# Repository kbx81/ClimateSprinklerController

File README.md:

# kbx's Climate and Sprinkler Controller

## A DIY Thermostat and/or Sprinkler (Valve) Controller

Here you'll find plans for an ESP32-based controller designed with [ESPHome](https://esphome.io) in mind. It is primarily designed for switching 24-volt AC circuits but it is flexible by design and should be adaptable to other types of electrical workloads.

In the [Preface](PREFACE.md) you will find background information about this project such as how it came to be and some personal thoughts and experiences I've had with home automation through the years.

In the [Hardware](HARDWARE.md) document you will find a general explanation of the theory of operation of a thermostat as well as a design overview of this device, some handy tips (should you choose to build one), construction, usage, and installation detail.

Finally, the [Hardware Detail](HARDWARE_DETAIL.md) document aims to explain why I did what I did -- design decisions, etc.

## Design Versions

At present there are two major "versions" of (iterations on?) the device -- a version that supports an OLED display such as the [SSD1325](https://www.adafruit.com/product/2674) and a version (well, actually three versions) that supports a Nextion touchscreen display. The project files for each can be found in its respective directory:
 - OLED versions:
   - [Version 2 (WROOM)](WROOM/)
   - [Version 3 (WROVER)](WROVER/)
 - Nextion versions:
   - [Nextion 3.5"](WROVER-Nextion3.5/) (contains no switching hardware!)
   - [Nextion 5"](WROVER-Nextion5/)
   - [Nextion 7"](WROVER-Nextion7/)

## PCB and BoMs

The schematic and PCB were drawn in [KiCAD](https://www.kicad.org). I had PCBs fabricated by [Elecrow](https://www.elecrow.com) but nearly any PCB fabricator should be able to manufacture these without any issues.

On [Octopart](https://octopart.com) I have posted a bill of materials (BoM) for each design version:
 - OLED versions:
   - [Version 2 (WROOM)](https://octopart.com/bom-tool/XvGbAePy)
   - [Version 3 (WROVER)](https://octopart.com/bom-tool/vZKpLnMD)
 - Nextion versions:
   - [Nextion 3.5"](https://octopart.com/bom-tool/dj6BW0gV) (contains no switching hardware!)
   - [Nextion 5"](https://octopart.com/bom-tool/kHZhyfjO)
   - [Nextion 7"](https://octopart.com/bom-tool/b5Lb00Zs)

### Important!

**Save money** by reading through the [build guide](HARDWARE.md) **before** you order any parts, as you likely _do not need **every** part in the linked BoMs!_ (For example, there are footprints multiple sensors on each PCB. You do not need all of the sensors!)

## ESPHome Configuration & Code

I've created a separate repository for my [ESPHome](https://esphome.io) [configurations](https://github.com/kbx81/esphome-configs); if you're looking for a starting point/example configuration, please have a look there.

## Legal stuff and License

Everything you see here is provided to you free of charge. You are free to use it however you please within the constraints of the license -- but you do so at your own risk. I accept absolutely no liability if you cause damage to your property, HVAC system, or any other hardware you choose to connect to this device.

The circuit schematics, PCBs and enclosures found here are licensed under the [Creative Commons Attribution-ShareAlike 4.0 International License](http://creativecommons.org/licenses/by-sa/4.0/).

_Thanks for visiting!_

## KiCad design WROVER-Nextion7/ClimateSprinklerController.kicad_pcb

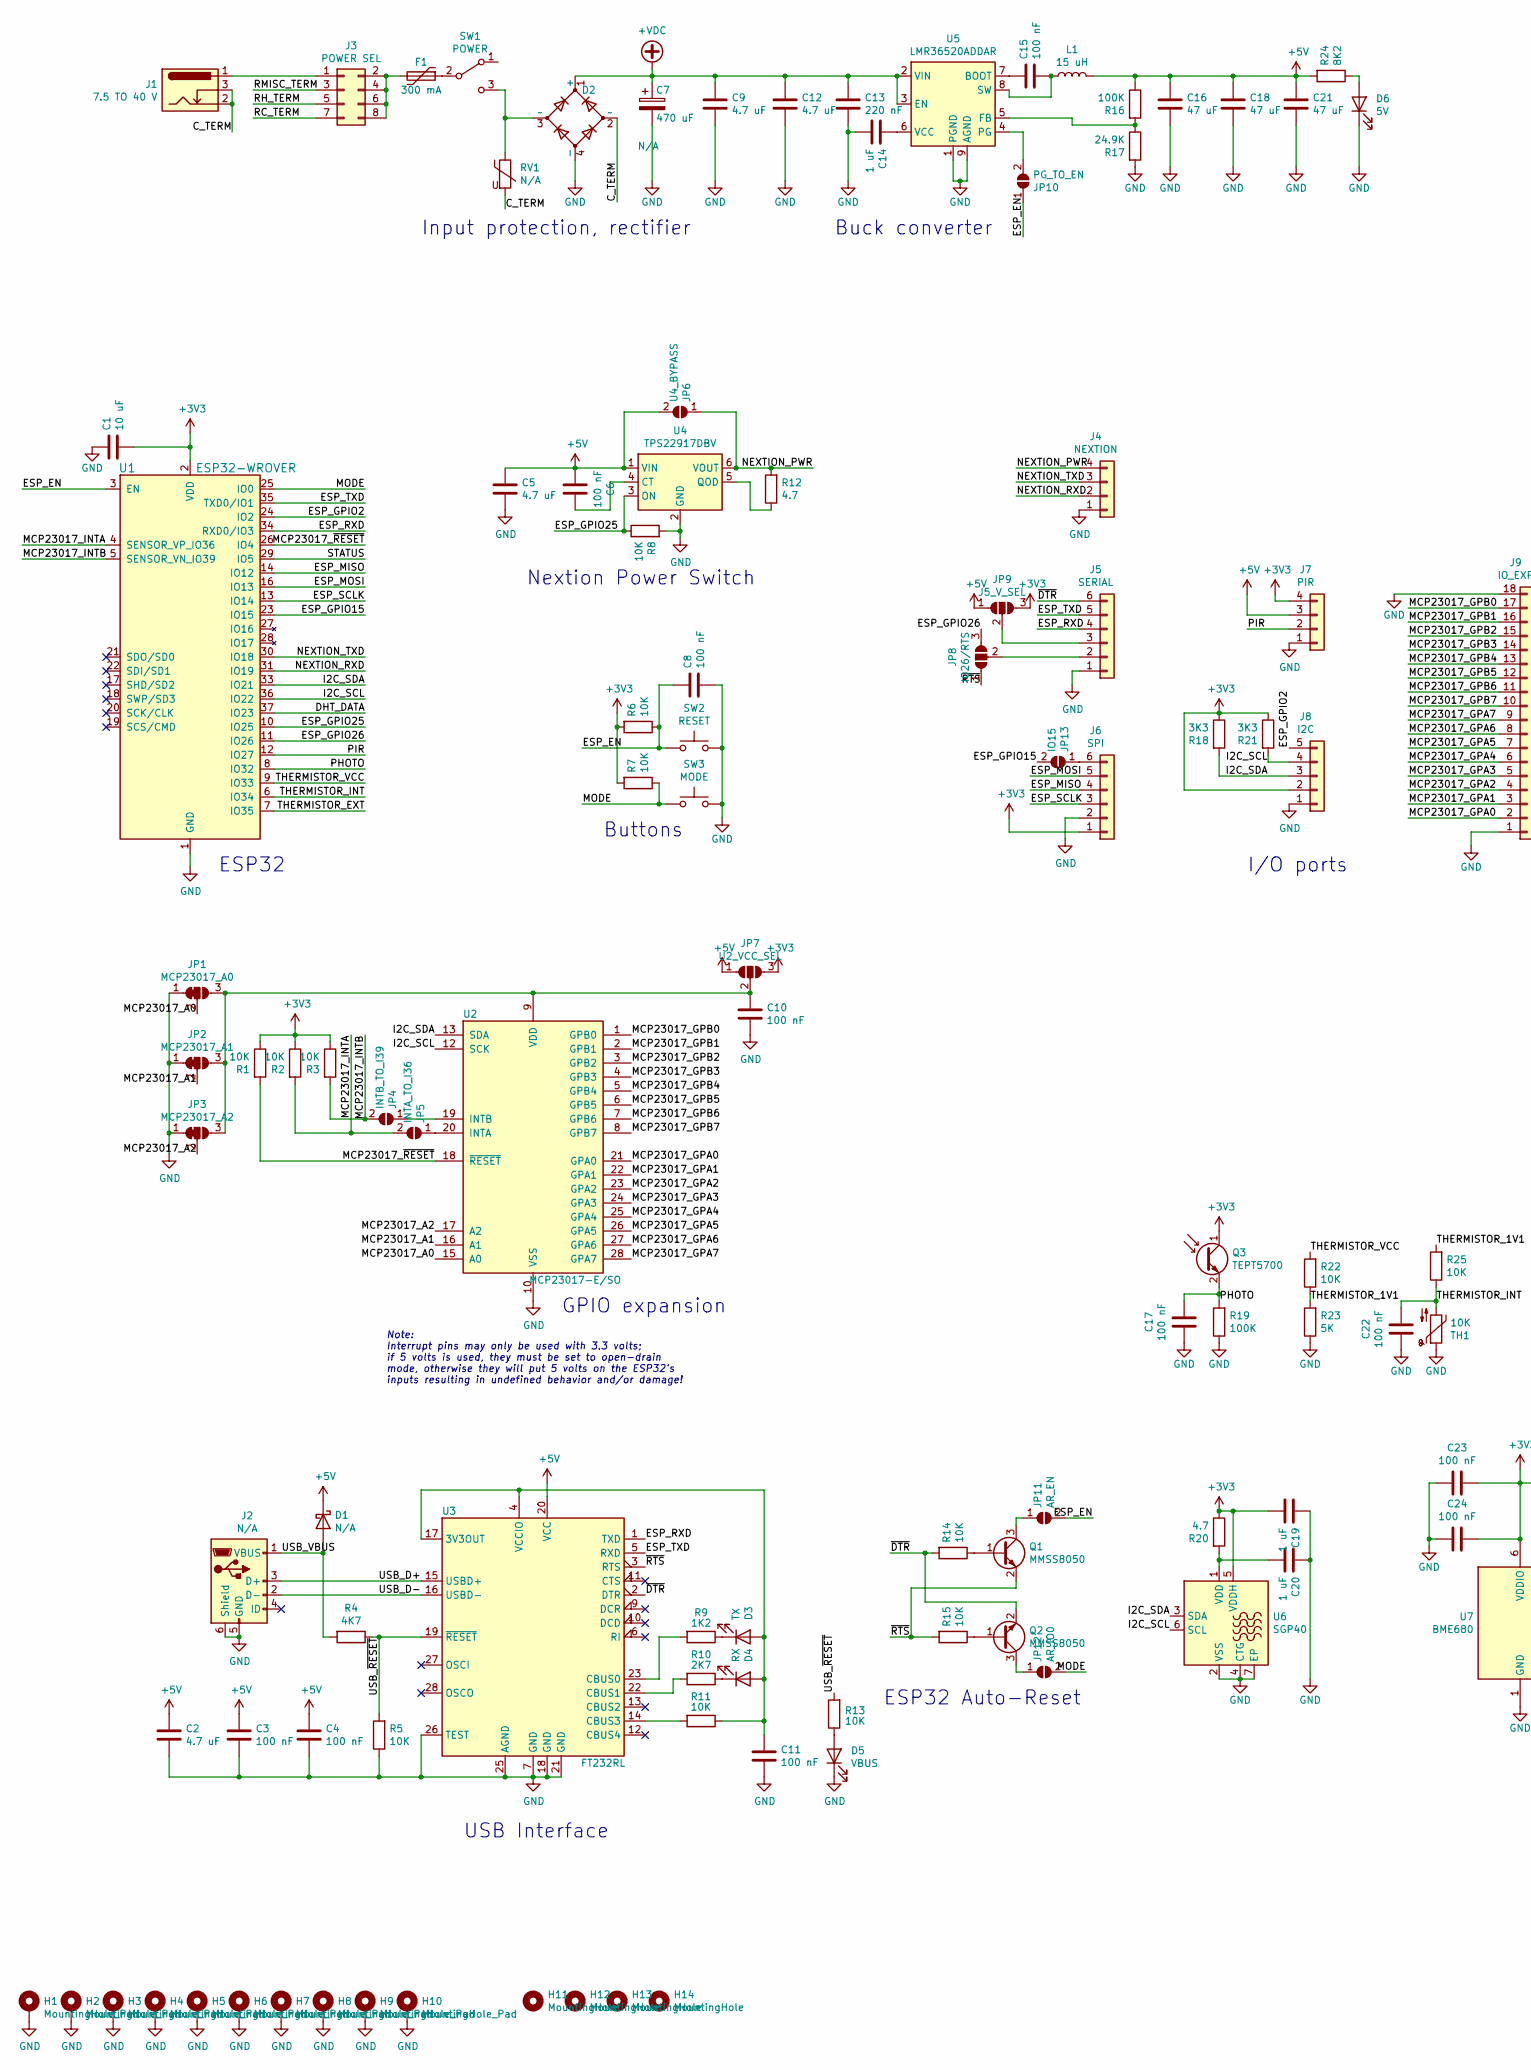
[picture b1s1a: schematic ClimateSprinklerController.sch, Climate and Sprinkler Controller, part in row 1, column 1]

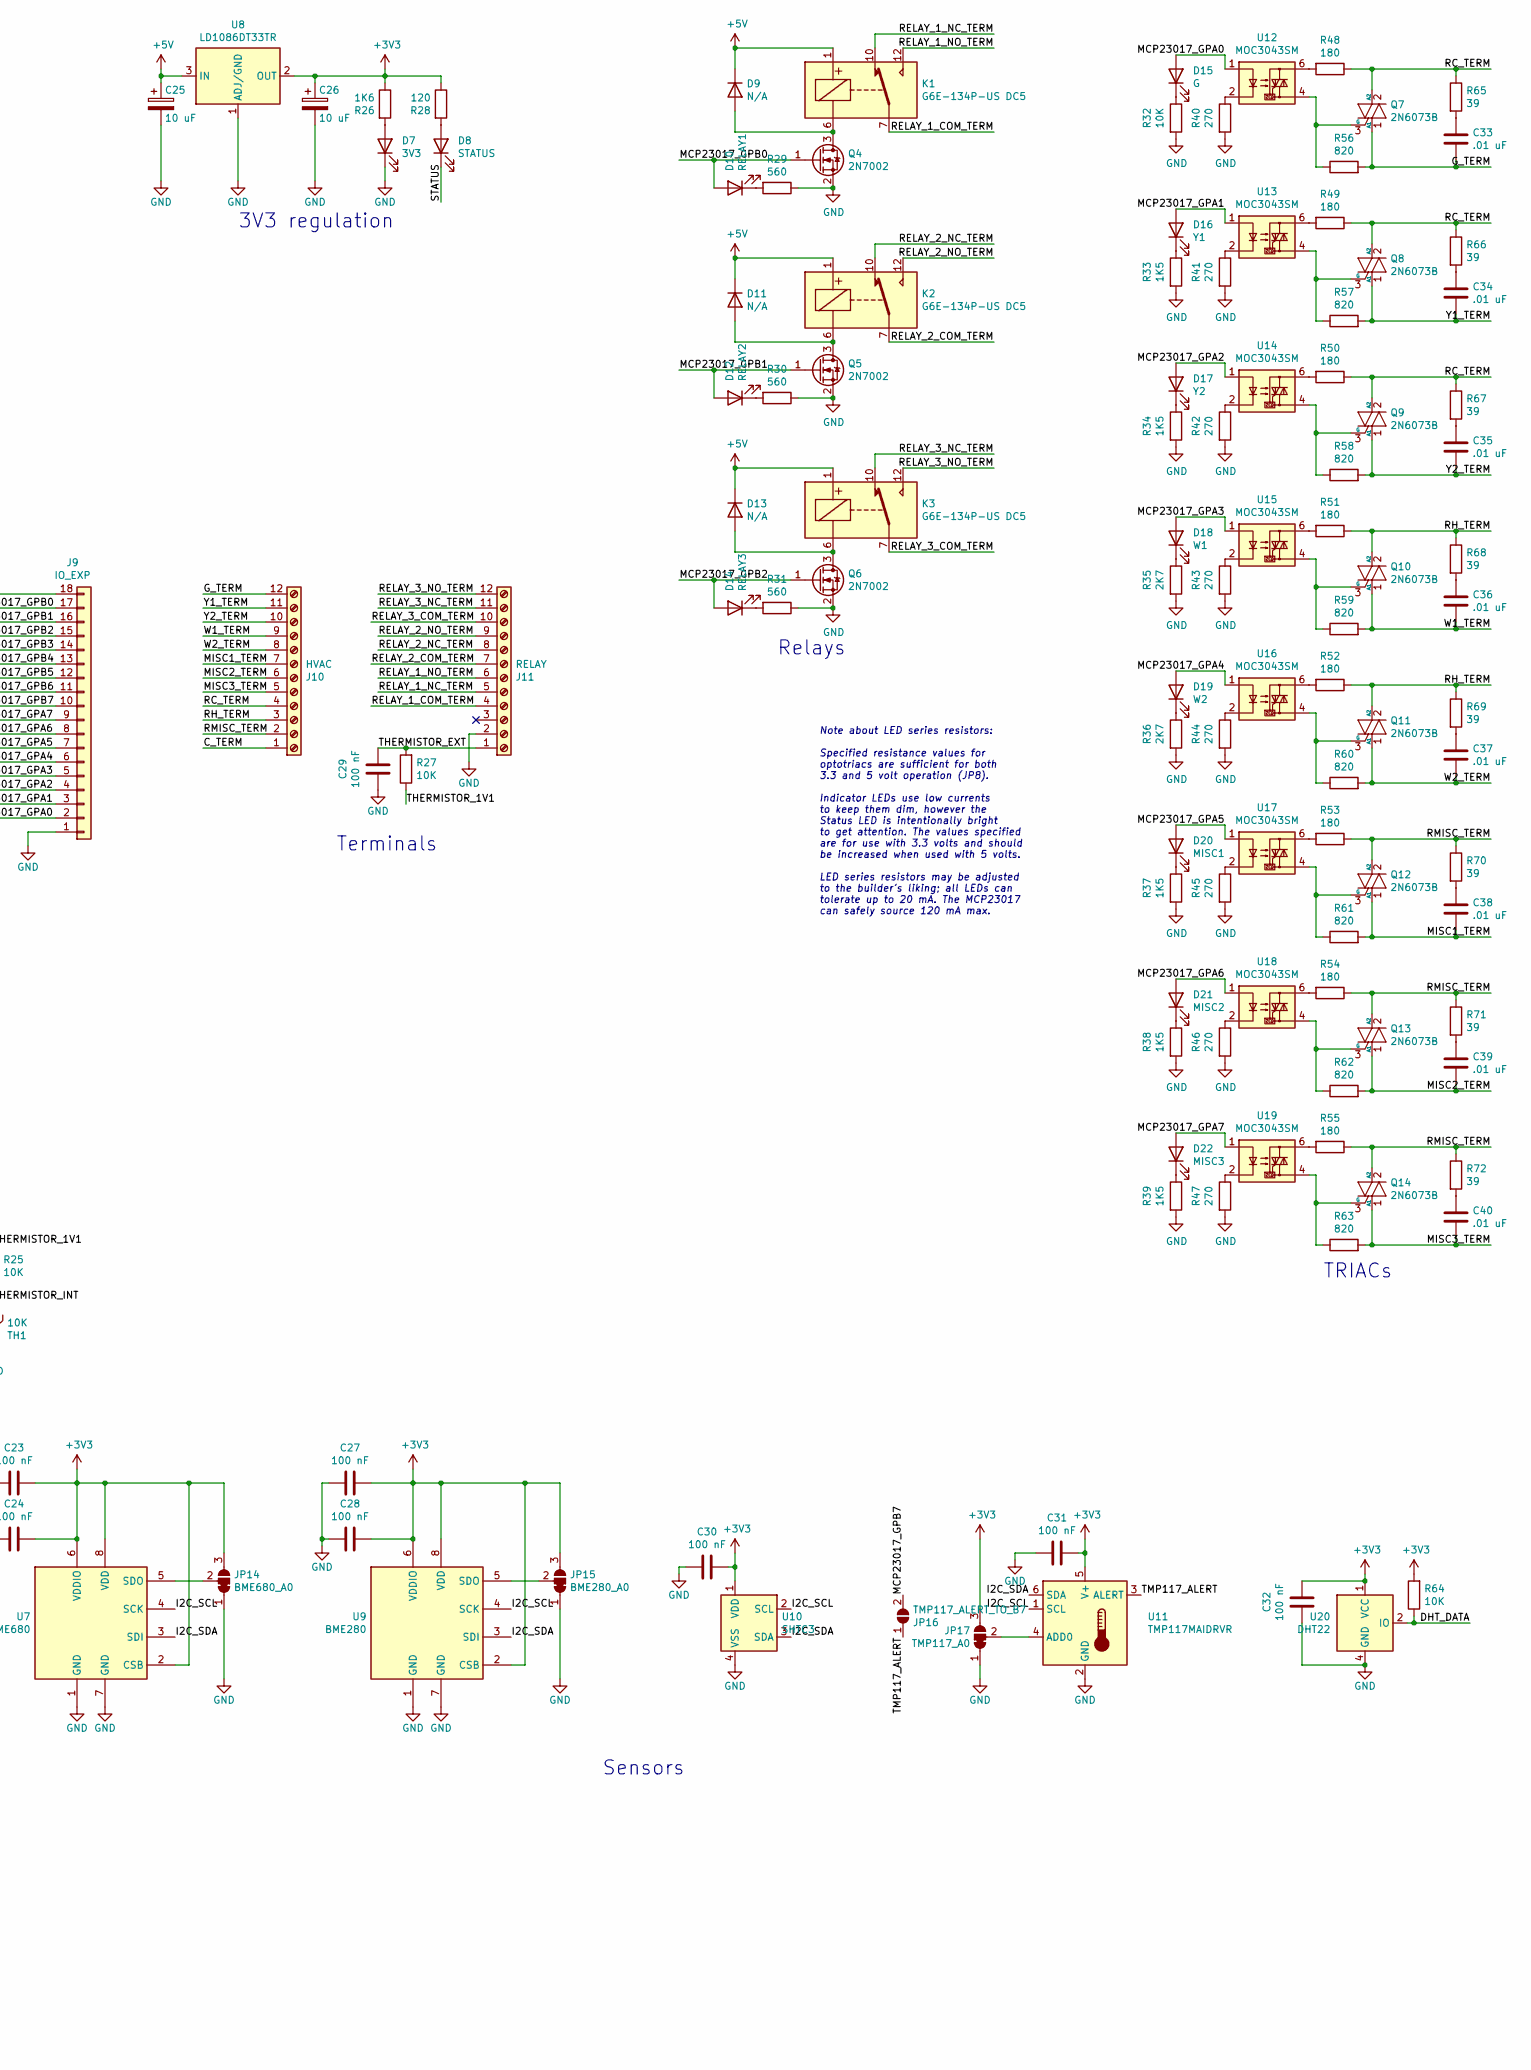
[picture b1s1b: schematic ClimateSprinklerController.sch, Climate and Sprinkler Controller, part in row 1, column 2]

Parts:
C1: 10 uF; C_0805_2012Metric; MPN1 C2012X5R1V106K085AC
C2, C5, C9, C12: 4.7 uF; C_0805_2012Metric; MPN1 C2012X5R1H475K125AB
C3, C4, C6, C8, C10, C11, C15, C17, C22, C23, C24, C27, C28, C29, C30, C31, C32: 100 nF; C_0805_2012Metric; MPN1 CC0805KRX7R7BB104
C7: 470 uF; CP_Radial_Cutout_L20.0mm_D10.0mm_P5.00mm; MPN1 UVK1H471MPD
C13: 220 nF; C_0805_2012Metric; MPN1 C2012X5R1H224K125AA
C14, C19, C20: 1 uF; C_0805_2012Metric; MPN1 C0805C105K4RACTU
C16, C18, C21: 47 uF; C_1210_3225Metric; MPN1 GRM32ER61C476KE15L
C25, C26: 10 uF; CP_Elec_5x5.8; MPN1 EEE-HP0J100R
C33, C34, C35, C36, C37, C38, C39, C40: .01 uF; C_0805_2012Metric; MPN1 CC0805KRX7R9BB103
D1: N/A; D_SOD-123F; MPN1 MBR230S1F-7
D2: N/A; Diode_Bridge_Bourns_CD-MBL2xxS; MPN1 CD-MBL206SL
D3: TX; LED_1206_3216Metric_ReverseMount_Hole1.8x2.4mm; MPN1 APTL3216QBC/D
D4: RX; LED_1206_3216Metric_ReverseMount_Hole1.8x2.4mm; MPN1 APTL3216SURCK
D5: VBUS; LED_1206_3216Metric_ReverseMount_Hole1.8x2.4mm; MPN1 APTL3216ZGC
D6: 5V; LED_1206_3216Metric_ReverseMount_Hole1.8x2.4mm; MPN1 597-6901-607F
D7: 3V3; LED_1206_3216Metric_ReverseMount_Hole1.8x2.4mm; MPN1 597-6901-607F
D8: STATUS; LED_1206_3216Metric_ReverseMount_Hole1.8x2.4mm; MPN1 APTL3216SECK
D9, D11, D13: N/A; D_SOD-123; MPN1 1N4148W
D10: RELAY1; LED_1206_3216Metric_ReverseMount_Hole1.8x2.4mm; MPN1 APTL3216CGCK
D12: RELAY2; LED_1206_3216Metric_ReverseMount_Hole1.8x2.4mm; MPN1 APTL3216CGCK
D14: RELAY3; LED_1206_3216Metric_ReverseMount_Hole1.8x2.4mm; MPN1 APTL3216CGCK
D15: G; LED_1206_3216Metric_ReverseMount_Hole1.8x2.4mm; MPN1 APTL3216ZGC
D16: Y1; LED_1206_3216Metric_ReverseMount_Hole1.8x2.4mm; MPN1 APTL3216QBC/D
D17: Y2; LED_1206_3216Metric_ReverseMount_Hole1.8x2.4mm; MPN1 APTL3216QBC/D
D18: W1; LED_1206_3216Metric_ReverseMount_Hole1.8x2.4mm; MPN1 APTL3216SURCK
D19: W2; LED_1206_3216Metric_ReverseMount_Hole1.8x2.4mm; MPN1 APTL3216SURCK
D20: MISC1; LED_1206_3216Metric_ReverseMount_Hole1.8x2.4mm; MPN1 APTL3216SYCK
D21: MISC2; LED_1206_3216Metric_ReverseMount_Hole1.8x2.4mm; MPN1 APTL3216SYCK
D22: MISC3; LED_1206_3216Metric_ReverseMount_Hole1.8x2.4mm; MPN1 APTL3216SYCK
F1: 300 mA; Fuse_2920_7451Metric; MPN1 2920L030DR
H1, H2, H3, H4, H5, H6: MountingHole_Pad; MountingHole_3.2mm_M3_Pad_Via; MPN1 N/A
H7, H8, H9, H10: MountingHole_Pad; MountingHole_3.2mm_M3_DIN965_Pad; MPN1 N/A
H11, H12, H13, H14: MountingHole; MountingHole_4.3mm_M4_DIN965_Pad; MPN1 N/A
J1: 7.5 TO 40 V; BarrelJack_Horizontal; MPN1 694106301002
J2: N/A; USB_Micro-B_Molex-105017-0001; MPN1 105017-0001
J3: POWER SEL; PinHeader_2x04_P2.54mm_Vertical; MPN1 N/A
J4: NEXTION; PinSocket_1x04_P2.54mm_Vertical; MPN1 N/A
J5: SERIAL; PinSocket_1x06_P2.54mm_Vertical; MPN1 N/A
J6: SPI; PinSocket_1x06_P2.54mm_Vertical; MPN1 N/A
J7: PIR; PinSocket_1x04_P2.54mm_Vertical; MPN1 N/A
J8: I2C; PinSocket_1x05_P2.54mm_Vertical; MPN1 N/A
J9: IO_EXP; PinSocket_1x18_P2.54mm_Vertical; MPN1 N/A
J10: HVAC; PhoenixContact_SPTAF_1_12-3.5-IL_1x12_P3.50mm_Vertical; MPN1 1862039
J11: RELAY; PhoenixContact_SPTAF_1_12-3.5-IL_1x12_P3.50mm_Vertical; MPN1 1862039
JP1: MCP23017_A0; SolderJumper-3_P1.3mm_Bridged12_RoundedPad1.0x1.5mm; MPN1 N/A
JP2: MCP23017_A1; SolderJumper-3_P1.3mm_Bridged12_RoundedPad1.0x1.5mm; MPN1 N/A
JP3: MCP23017_A2; SolderJumper-3_P1.3mm_Bridged12_RoundedPad1.0x1.5mm; MPN1 N/A
JP4: INTB_TO_I39; SolderJumper-2_P1.3mm_Open_RoundedPad1.0x1.5mm; MPN1 N/A
JP5: INTA_TO_I36; SolderJumper-2_P1.3mm_Open_RoundedPad1.0x1.5mm; MPN1 N/A
JP6: U4_BYPASS; SolderJumper-2_P1.3mm_Open_RoundedPad1.0x1.5mm; MPN1 N/A
JP7: U2_VCC_SEL; SolderJumper-3_P1.3mm_Open_RoundedPad1.0x1.5mm; MPN1 N/A
JP8: IO26/RTS; SolderJumper-3_P1.3mm_Open_RoundedPad1.0x1.5mm; MPN1 N/A
JP9: J5_V_SEL; SolderJumper-3_P1.3mm_Open_RoundedPad1.0x1.5mm; MPN1 N/A
JP10: PG_TO_EN; SolderJumper-2_P1.3mm_Open_RoundedPad1.0x1.5mm; MPN1 N/A
JP11: AR_EN; SolderJumper-2_P1.3mm_Open_RoundedPad1.0x1.5mm; MPN1 N/A
JP12: AR_IO0; SolderJumper-2_P1.3mm_Open_RoundedPad1.0x1.5mm; MPN1 N/A
JP13: IO15; SolderJumper-2_P1.3mm_Open_RoundedPad1.0x1.5mm; MPN1 N/A
JP14: BME680_A0; SolderJumper-3_P1.3mm_Bridged12_RoundedPad1.0x1.5mm; MPN1 N/A
JP15: BME280_A0; SolderJumper-3_P1.3mm_Bridged12_RoundedPad1.0x1.5mm; MPN1 N/A
JP16: TMP117_ALERT_TO_B7; SolderJumper-2_P1.3mm_Open_RoundedPad1.0x1.5mm; MPN1 N/A
JP17: TMP117_A0; SolderJumper-3_P1.3mm_Bridged12_RoundedPad1.0x1.5mm; MPN1 N/A
K1, K2, K3: G6E-134P-US DC5; Relay_SPDT_Omron_G6E; MPN1 G6E-134P-US DC5
L1: 15 uH; L_Wuerth_WE-PD-Typ-LS; MPN1 7447709150
Q1, Q2: MMSS8050; SOT-23; MPN1 MMSS8050
Q3: TEPT5700; LED_D5.0mm_Clear; MPN1 TEPT5700
Q4, Q5, Q6: 2N7002; SOT-23; MPN1 2N7002
Q7, Q8, Q9, Q10, Q11, Q12, Q13, Q14: 2N6073B; TO-225-3_Vertical; MPN1 2N6073BG
R1, R2, R3, R5, R6, R7, R8, R11, R13, R14, R15, R22, R25, R27, R32, R64: 10K; R_0805_2012Metric_Pad1.20x1.40mm_HandSolder; MPN1 RC0805FR-0710KL
R4: 4K7; R_0805_2012Metric_Pad1.20x1.40mm_HandSolder; MPN1 RT0805FRE074K7L
R9: 1K2; R_0805_2012Metric_Pad1.20x1.40mm_HandSolder; MPN1 RT0805FRE072K7L
R10, R35, R36: 2K7; R_0805_2012Metric_Pad1.20x1.40mm_HandSolder; MPN1 RT0805FRE072K7L
R12, R20: 4.7; R_0805_2012Metric_Pad1.20x1.40mm_HandSolder; MPN1 RC0805FR-074R7L
R16, R19: 100K; R_0805_2012Metric_Pad1.20x1.40mm_HandSolder; MPN1 RC0805FR-07100KL
R17: 24.9K; R_0805_2012Metric_Pad1.20x1.40mm_HandSolder; MPN1 RT0805FRE0724K9L
R18, R21: 3K3; R_0805_2012Metric_Pad1.20x1.40mm_HandSolder; MPN1 RT0805FRE073K3L
R23: 5K; R_0805_2012Metric_Pad1.20x1.40mm_HandSolder; MPN1 CRCW08055K00JNTA
R24: 8K2; R_0805_2012Metric_Pad1.20x1.40mm_HandSolder; MPN1 RT0805FRE078K2L
R26: 1K6; R_0805_2012Metric_Pad1.20x1.40mm_HandSolder; MPN1 RT0805FRE071K6L
R28: 120; R_0805_2012Metric_Pad1.20x1.40mm_HandSolder; MPN1 RT0805FRE07120RL
R29, R30, R31: 560; R_0805_2012Metric_Pad1.20x1.40mm_HandSolder; MPN1 RT0805FRE07560RL
R33, R34, R37, R38, R39: 1K5; R_0805_2012Metric_Pad1.20x1.40mm_HandSolder; MPN1 RT0805FRE071K5L
R40, R41, R42, R43, R44, R45, R46, R47: 270; R_0805_2012Metric_Pad1.20x1.40mm_HandSolder; MPN1 RT0805FRE07270RL
R48, R49, R50, R51, R52, R53, R54, R55: 180; R_0805_2012Metric_Pad1.20x1.40mm_HandSolder; MPN1 RT0805FRE07180RL
R56, R57, R58, R59, R60, R61, R62, R63: 820; R_0805_2012Metric_Pad1.20x1.40mm_HandSolder; MPN1 RT0805FRE07820RL
R65, R66, R67, R68, R69, R70, R71, R72: 39; R_0805_2012Metric_Pad1.20x1.40mm_HandSolder; MPN1 ERJ-P06J390V
RV1: N/A; RV_Disc_D7mm_W4mm_P5mm; MPN1 B72205S0400K101
SW1: POWER; SW_Push_1P2T_Vertical_E-Switch_800UDP8P1A1M6; MPN1 48BFSP1M6QT
SW2: RESET; SW_Tactile_SPST_Angled_PTS645Vx58-2LFS; MPN1 PTS645VK582LFS
SW3: MODE; SW_Tactile_SPST_Angled_PTS645Vx58-2LFS; MPN1 PTS645VK582LFS
TH1: 10K; PinSocket_1x02_P2.54mm_Vertical; MPN1 NXFT15XH103FA2B100
U1: ESP32-WROVER; MPN1 ESP32-WROVER
U2: MCP23017-E/SO; SOIC-28W_7.5x17.9mm_P1.27mm; MPN1 MCP23017-E/SO
U3: FT232RL; SSOP-28_5.3x10.2mm_P0.65mm; MPN1 FT232RL
U4: TPS22917DBV; SOT-23-6; MPN1 TPS22917DBV
U5: LMR36520ADDAR; Texas_HSOP-8-1EP_3.9x4.9mm_P1.27mm_ThermalVias; MPN1 LMR36520ADDAR
U6: SGP40; DFN-6-1EP_2.44x2.44mm_P0.8mm_EP1.25x1.7mm; MPN1 SGP40
U7: BME680; Bosch_LGA-8_3x3mm_P0.8mm_ClockwisePinNumbering; MPN1 BME680
U8: LD1086DT33TR; TO-252-2; MPN1 LD1086DT33TR
U9: BME280; Bosch_LGA-8_2.5x2.5mm_P0.65mm_ClockwisePinNumbering; MPN1 BME280
U10: SHTC3; AMS_QFN-4-1EP_2x2mm_P0.95mm_EP0.7x1.6mm; MPN1 SHTC3
U11: TMP117MAIDRVR; WSON-6-1EP_2x2mm_P0.65mm_EP1x1.6mm; MPN1 TMP117MAIDRVR
U12, U13, U14, U15, U16, U17, U18, U19: MOC3043SM; SMDIP-6_W9.53mm; MPN1 MOC3043SM
U20: DHT22; PinSocket_1x04_P2.54mm_Vertical; MPN1 DHT22

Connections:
+3V3: C1.2, C19.2, C23.1, C24.1, C26.1, C27.1, C28.1, C30.1, C31.1, C32.1, J6.1, J7.4, J8.2, JP7.3 (B), JP9.3 (B), JP14.3 (B), JP15.3 (B), JP17.3 (B), Q3.1 (C), R1.1, R2.1, R3.1, R6.2, R7.2, R18.1, R20.1, R21.1, R26.1, R28.1, R64.2, U1.2 (VDD), U6.5 (VDDH), U7.2 (CSB), U7.6 (VDDIO), U7.8 (VDD), U8.2 (OUT), U9.2 (CSB), U9.6 (VDDIO), U9.8 (VDD), U10.1 (VDD), U11.5 (V+), U20.1 (VCC)
+5V: C2.1, C3.1, C4.1, C5.1, C6.2, C16.1, C18.1, C21.1, C25.1, D1.1 (K), D9.1 (K), D11.1 (K), D13.1 (K), J7.3, JP6.2 (B), JP7.1 (A), JP9.1 (A), K1.1, K2.1, K3.1, L1.2, R16.1, R24.2, U3.20 (VCC), U4.1 (VIN), U8.3 (IN)
+VDC: C7.1, C9.1, C12.1, C13.1, D2.1 (+), U5.2 (VIN), U5.3 (EN)
/C_TERM: D2.2 (~~), J1.2, J1.3, J10.1, RV1.2
/DHT_DATA: R64.1, U1.37 (IO23), U20.2 (IO)
/ESP_EN: C8.1, JP10.1 (A), JP11.2 (B), R6.1, SW2.2, U1.3 (EN)
/ESP_GPIO2: J8.5, U1.24 (IO2)
/ESP_GPIO15: JP13.2 (B), U1.23 (IO15)
/ESP_GPIO25: R8.1, U1.10 (IO25), U4.3 (ON)
/ESP_GPIO26: JP8.3 (B), U1.11 (IO26)
/ESP_MISO: J6.4, U1.14 (IO12)
/ESP_MOSI: J6.5, U1.16 (IO13)
/ESP_RXD: J5.4, U1.34 (RXD0/IO3), U3.1 (TXD)
/ESP_SCLK: J6.3, U1.13 (IO14)
/ESP_TXD: J5.5, U1.35 (TXD0/IO1), U3.5 (RXD)
/G_TERM: C33.2, J10.12, Q7.1 (A1), R56.2
/I2C_SCL: J8.4, R21.2, U1.36 (IO22), U2.12 (SCK), U6.6 (SCL), U7.4 (SCK), U9.4 (SCK), U10.2 (SCL), U11.1 (SCL)
/I2C_SDA: J8.3, R18.2, U1.33 (IO21), U2.13 (SDA), U6.3 (SDA), U7.3 (SDI), U9.3 (SDI), U10.3 (SDA), U11.6 (SDA)
/MCP23017_A0: JP1.2 (C), U2.15 (A0)
/MCP23017_A1: JP2.2 (C), U2.16 (A1)
/MCP23017_A2: JP3.2 (C), U2.17 (A2)
/MCP23017_GPA0: D15.2 (A), J9.2, U2.21 (GPA0), U12.1
/MCP23017_GPA1: D16.2 (A), J9.3, U2.22 (GPA1), U13.1
/MCP23017_GPA2: D17.2 (A), J9.4, U2.23 (GPA2), U14.1
/MCP23017_GPA3: D18.2 (A), J9.5, U2.24 (GPA3), U15.1
/MCP23017_GPA4: D19.2 (A), J9.6, U2.25 (GPA4), U16.1
/MCP23017_GPA5: D20.2 (A), J9.7, U2.26 (GPA5), U17.1
/MCP23017_GPA6: D21.2 (A), J9.8, U2.27 (GPA6), U18.1
/MCP23017_GPA7: D22.2 (A), J9.9, U2.28 (GPA7), U19.1
/MCP23017_GPB0: D10.2 (A), J9.17, Q4.1 (G), U2.1 (GPB0)
/MCP23017_GPB1: D12.2 (A), J9.16, Q5.1 (G), U2.2 (GPB1)
/MCP23017_GPB2: D14.2 (A), J9.15, Q6.1 (G), U2.3 (GPB2)
/MCP23017_GPB3: J9.14, U2.4 (GPB3)
/MCP23017_GPB4: J9.13, U2.5 (GPB4)
/MCP23017_GPB5: J9.12, U2.6 (GPB5)
/MCP23017_GPB6: J9.11, U2.7 (GPB6)
/MCP23017_GPB7: J9.10, JP16.2 (B), U2.8 (GPB7)
/MCP23017_INTA: JP5.2 (B), R2.2, U1.4 (SENSOR_VP_IO36)
/MCP23017_INTB: JP4.2 (B), R3.2, U1.5 (SENSOR_VN_IO39)
/MCP23017_~RESET: R1.2, U1.26 (IO4), U2.18 (~RESET~)
/MISC1_TERM: C38.2, J10.7, Q12.1 (A1), R61.2
/MISC2_TERM: C39.2, J10.6, Q13.1 (A1), R62.2
/MISC3_TERM: C40.2, J10.5, Q14.1 (A1), R63.2
/MODE: JP12.2 (B), R7.1, SW3.1, U1.25 (IO0)
/NEXTION_PWR: J4.4, JP6.1 (A), R12.2, U4.6 (VOUT)
/NEXTION_RXD: J4.2, U1.31 (IO19)
/NEXTION_TXD: J4.3, U1.30 (IO18)
/PHOTO: C17.1, Q3.2 (E), R19.2, U1.8 (IO32)
/PIR: J7.2, U1.12 (IO27)
/RC_TERM: J3.7, J10.4, Q7.2 (A2), Q8.2 (A2), Q9.2 (A2), R48.1, R49.1, R50.1, R65.1, R66.1, R67.1
/RELAY_1_COM_TERM: J11.4, K1.7
/RELAY_1_NC_TERM: J11.5, K1.10
/RELAY_1_NO_TERM: J11.6, K1.12
/RELAY_2_COM_TERM: J11.7, K2.7
/RELAY_2_NC_TERM: J11.8, K2.10
/RELAY_2_NO_TERM: J11.9, K2.12
/RELAY_3_COM_TERM: J11.10, K3.7
/RELAY_3_NC_TERM: J11.11, K3.10
/RELAY_3_NO_TERM: J11.12, K3.12
/RH_TERM: J3.5, J10.3, Q10.2 (A2), Q11.2 (A2), R51.1, R52.1, R68.1, R69.1
/RMISC_TERM: J3.3, J10.2, Q12.2 (A2), Q13.2 (A2), Q14.2 (A2), R53.1, R54.1, R55.1, R70.1, R71.1, R72.1
/STATUS: D8.1 (K), U1.29 (IO5)
/THERMISTOR_1V1: R22.1, R23.2, R25.2, R27.1
/THERMISTOR_EXT: C29.1, J11.1, R27.2, U1.7 (IO35)
/THERMISTOR_INT: C22.1, R25.1, TH1.2, U1.6 (IO34)
/THERMISTOR_VCC: R22.2, U1.9 (IO33)
/TMP117_ALERT: JP16.1 (A), U11.3 (ALERT)
/USB_D+: J2.3 (D+), U3.15 (USBD+)
/USB_D-: J2.2 (D-), U3.16 (USBD-)
/USB_VBUS: D1.2 (A), J2.1 (VBUS), R4.2
/USB_~RESET: R4.1, R5.2, R13.2, U3.19 (~RESET~)
/W1_TERM: C36.2, J10.9, Q10.1 (A1), R59.2
/W2_TERM: C37.2, J10.8, Q11.1 (A1), R60.2
/Y1_TERM: C34.2, J10.11, Q8.1 (A1), R57.2
/Y2_TERM: C35.2, J10.10, Q9.1 (A1), R58.2
/~DTR: J5.6, Q2.2 (E), R14.2, U3.2 (DTR)
/~RTS: JP8.1 (A), Q1.2 (E), R15.2, U3.3 (RTS)
GND: C1.1, C2.2, C3.2, C4.2, C5.2, C7.2, C8.2, C9.2, C10.2, C11.2, C12.2, C13.2, C14.2, C16.2, C17.2, C18.2, C19.1, C20.1, C21.2, C22.2, C23.2, C24.2, C25.2, C26.2, C27.2, C28.2, C29.2, C30.2, C31.2, C32.2, D2.4 (-), D5.1 (K), D6.1 (K), D7.1 (K), H1.1, H2.1, H3.1, H4.1, H5.1, H6.1, H7.1, H8.1, H9.1, H10.1, J2.5 (GND), J2.6 (Shield), J4.1, J5.1, J6.2, J7.1, J8.1, J9.1, J9.18, J11.2, JP1.1 (A), JP2.1 (A), JP3.1 (A), JP14.1 (A), JP15.1 (A), JP17.1 (A), Q4.2 (S), Q5.2 (S), Q6.2 (S), R5.1, R8.2, R17.2, R19.1, R23.1, R29.1, R30.1, R31.1, R32.2, R33.2, R34.2, R35.2, R36.2, R37.2, R38.2, R39.2, R40.2, R41.2, R42.2, R43.2, R44.2, R45.2, R46.2, R47.2, SW2.1, SW3.2, TH1.1, U1.1 (GND), U1.15 (GND), U1.38 (GND), U1.39 (GND), U2.10 (VSS), U3.7 (GND), U3.18 (GND), U3.21 (GND), U3.25 (AGND), U3.26 (TEST), U4.2 (GND), U5.1 (PGND), U5.9 (AGND), U6.2 (VSS), U6.4 (CTG), U6.7 (EP), U7.1 (GND), U7.7 (GND), U8.1 (ADJ/GND), U9.1 (GND), U9.7 (GND), U10.4 (VSS), U11.2 (GND), U20.4 (GND)
unnamed: C6.1, U4.4 (CT)
unnamed: C10.1, JP1.3 (B), JP2.3 (B), JP3.3 (B), JP7.2 (C), U2.9 (VDD)
unnamed: C11.1, D3.2 (A), D4.2 (A), R11.1, U3.4 (VCCIO), U3.17 (3V3OUT)
unnamed: C14.1, U5.6 (VCC)
unnamed: C15.1, U5.7 (BOOT)
unnamed: C15.2, L1.1, U5.8 (SW)
unnamed: C20.2, R20.2, U6.1 (VDD)
unnamed: C33.1, R65.2
unnamed: C34.1, R66.2
unnamed: C35.1, R67.2
unnamed: C36.1, R68.2
unnamed: C37.1, R69.2
unnamed: C38.1, R70.2
unnamed: C39.1, R71.2
unnamed: C40.1, R72.2
unnamed: D2.3 (~~), RV1.1, SW1.3 (C)
unnamed: D3.1 (K), R9.1
unnamed: D4.1 (K), R10.1
unnamed: D5.2 (A), R13.1
unnamed: D6.2 (A), R24.1
unnamed: D7.2 (A), R26.2
unnamed: D8.2 (A), R28.2
unnamed: D9.2 (A), K1.6, Q4.3 (D)
unnamed: D10.1 (K), R29.2
unnamed: D11.2 (A), K2.6, Q5.3 (D)
unnamed: D12.1 (K), R30.2
unnamed: D13.2 (A), K3.6, Q6.3 (D)
unnamed: D14.1 (K), R31.2
unnamed: D15.1 (K), R32.1
unnamed: D16.1 (K), R33.1
unnamed: D17.1 (K), R34.1
unnamed: D18.1 (K), R35.1
unnamed: D19.1 (K), R36.1
unnamed: D20.1 (K), R37.1
unnamed: D21.1 (K), R38.1
unnamed: D22.1 (K), R39.1
unnamed: F1.1, SW1.2 (B)
unnamed: F1.2, J3.2, J3.4, J3.6, J3.8
unnamed: J1.1, J3.1
unnamed: J5.2, JP8.2 (C)
unnamed: J5.3, JP9.2 (C)
unnamed: J6.6, JP13.1 (A)
unnamed: JP4.1 (A), U2.19 (INTB)
unnamed: JP5.1 (A), U2.20 (INTA)
unnamed: JP10.2 (B), U5.4 (PG)
unnamed: JP11.1 (A), Q1.3 (C)
unnamed: JP12.1 (A), Q2.3 (C)
unnamed: JP14.2 (C), U7.5 (SDO)
unnamed: JP15.2 (C), U9.5 (SDO)
unnamed: JP17.2 (C), U11.4 (ADD0)
unnamed: Q1.1 (B), R14.1
unnamed: Q2.1 (B), R15.1
unnamed: Q7.3 (G), R56.1, U12.4
unnamed: Q8.3 (G), R57.1, U13.4
unnamed: Q9.3 (G), R58.1, U14.4
unnamed: Q10.3 (G), R59.1, U15.4
unnamed: Q11.3 (G), R60.1, U16.4
unnamed: Q12.3 (G), R61.1, U17.4
unnamed: Q13.3 (G), R62.1, U18.4
unnamed: Q14.3 (G), R63.1, U19.4
unnamed: R9.2, U3.23 (CBUS0)
unnamed: R10.2, U3.22 (CBUS1)
unnamed: R11.2, U3.14 (CBUS3)
unnamed: R12.1, U4.5 (QOD)
unnamed: R16.2, R17.1, U5.5 (FB)
unnamed: R40.1, U12.2
unnamed: R41.1, U13.2
unnamed: R42.1, U14.2
unnamed: R43.1, U15.2
unnamed: R44.1, U16.2
unnamed: R45.1, U17.2
unnamed: R46.1, U18.2
unnamed: R47.1, U19.2
unnamed: R48.2, U12.6
unnamed: R49.2, U13.6
unnamed: R50.2, U14.6
unnamed: R51.2, U15.6
unnamed: R52.2, U16.6
unnamed: R53.2, U17.6
unnamed: R54.2, U18.6
unnamed: R55.2, U19.6

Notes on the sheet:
Buck converter
3V3 regulation
Relays
TRIACs
Terminals
I/O ports
ESP32
GPIO expansion
Buttons
Input protection, rectifier
Note: Interrupt pins may only be used with 3.3 volts; if 5 volts is used, they must be set to open-drain mode, otherwise they will put 5 volts on the ESP32’s inputs resulting in undefined behavior and/or damage!
Note about LED series resistors: Specified resistance values for optotriacs are sufficient for both 3.3 and 5 volt operation (JP8). Indicator LEDs use low currents to keep them dim, however the Status LED is intentionally bright to get attention. The values specified are for use with 3.3 volts and 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
Sensors
ESP32 Auto-Reset
USB Interface
Nextion Power Switch

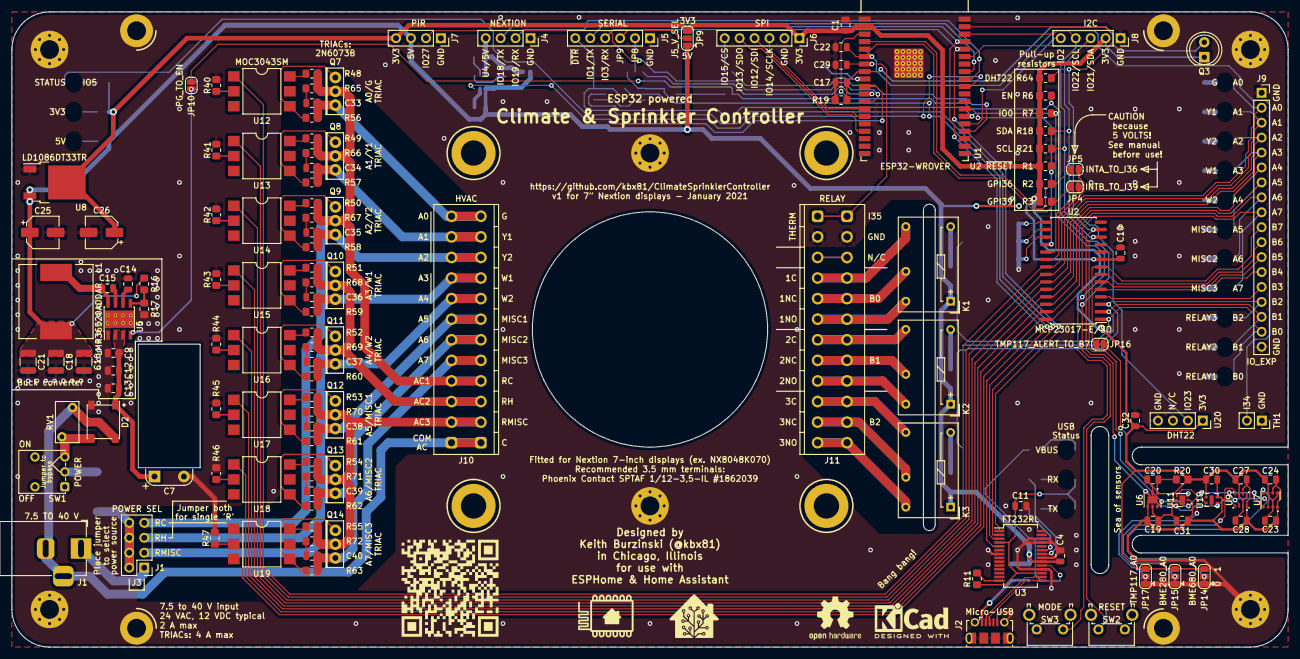
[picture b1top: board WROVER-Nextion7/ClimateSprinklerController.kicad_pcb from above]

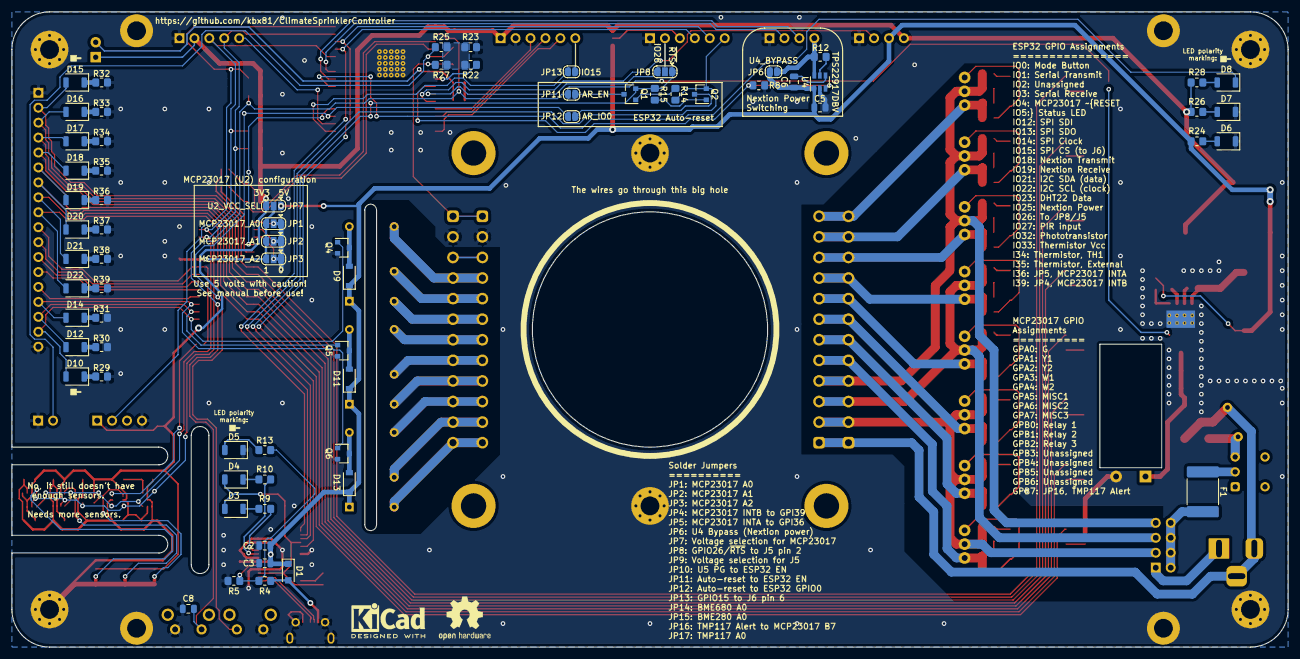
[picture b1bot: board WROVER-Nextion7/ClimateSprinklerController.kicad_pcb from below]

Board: 2 copper layers, 217.0 x 108.0 mm, 221 parts (69 on the bottom side), 159 nets.

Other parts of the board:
QR*****: ClimateSprinklerControllerQR
